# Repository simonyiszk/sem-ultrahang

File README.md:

# Ultrahangos hangszóró

## Célkitűzés 
A projekt során egy ultrahangos irányított hangszórót tervezünk és valósítunk meg először analóg, majd digitális elektronikai alkatrészek felhasználásával.
Az elkészült hangszórót standolásokon bemutatható kísérleti eszköznek szánjuk, az öncélú szórakozáson kívül (zenehallgatás) akusztikával kapcsolatos fizikai kísérletek szemléltetésére, mint például:
- hanghullámok terjedésének és tulajdonságainak vizsgálata
- ultrahangos lebegtetés

## Analóg verzió
A rendszer blokkvázlata az alábbi ábrán látható:

A jelforrást egyelőre nem specifikáltuk.
Az analóg verzióban PWM modulátort és a hozzá tartozó oszcillátort műveleti erősítőkkel valósítjuk meg.
Kapcsolóüzemű végerősítőfokozat gyanánt H-hidat, a prototípusban TC4427 típusú gate-meghajtó IC-t használunk. Hangszóróként az internetről rendelt 40 kHz rezonanciafrekvenciájú ultrahangos adó szolgál.

### Mérföldkövek

- [ ] **PWM modulátor műveleti erősítővel**
  - [X] Integrátor építése és mérése
  - [X] Hiszterézises komparátor építése és mérése
  - [X] Komplett prototípus megépítése breadboard-on
  - [ ] **Dokumentálás**
  - [ ] **Áramkörtervezés**
- [X] Jelforrás specifikációja
  - [X] Szükséges terveznivalók
- [X] Végfok
  - [X] H-híd tervezése (szükséges egyáltalán?)
- [ ] Hangszórómátrix
- [ ] Rendszerintegráció
  - [ ] NYÁK tervezés
  - [ ] Gyártás
  - [ ] Beültetés

### Side quest-ek
- [X] **Ultrahangos lebegtető**
  - [X] TC4427 tesztje
  - [X] **Oszcillátor aszimmetrikus táplálásának megoldása**
  - [X] **Hullámhossz meghatározása a pozicionáláshoz**
  - [X] Önjáró prototípus megépítése (amihez csak táp kell, és működik)
- [ ] Tápegység tervezése
  - TBD

## Digitális verzió
(Még nem tartunk itt... egyébként a [2025-ös tanfolyampanelt](https://github.com/simonyiszk/sem-armpanel-2025) szeretnénk hozzá használni.)

## Dokumentáció
A hierarchikus schematic dokumentációja [itt](./docs/hierarchia.md) érhető el.

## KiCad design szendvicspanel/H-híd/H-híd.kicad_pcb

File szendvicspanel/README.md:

# Szendvicspanel

## Megtervezendő:
 - [ ] board mérete
 - [ ] lábak száma, lábkiosztás az összes modult figyelembe véve (ld: [rendszerterv](../rendszerterv.txt))
 - [ ] legyenek-e átkonfigurálhatók a lábak (pl. jumperekkel)
 - [ ] analóg modul a jelgenerátorra
   - [ ] schematic
   - [ ] PCB
 - [ ] BOOST-konverteres tápegység
   - [ ] schematic
   - [ ] PCB
 - [ ] jelgenerátor PCB
 - [ ] H-híd + driver PCB
 - [ ] mikrokontroller PCB

## Mikrokontroller pinout

 - **a kép vízszintesen tükrözve van**
 - socketek kellenek neki
 - lehet-e neki tápot adni?

## WIP:
jelgenerátor modul PCB (ld: `jelgen.kicad_pro`)
 - opamp a REF feszültségen
 - PWM generátor
 - az analóg input jelenleg hanging:(
 - 10x10 cm, pazarló a hellyel
 - 2x10 pin, csak 4-et használ
 - egyoldalú, THT
 - teszt pontok még kellenek rá
 - még van mit pofozni rajta

H-híd + driver PCB (ld: `hbridge.kicad_pro`)
 - P-csatornás FET-ek a híd felére, vezérlőjelek átkötve
 - PCB még nincs

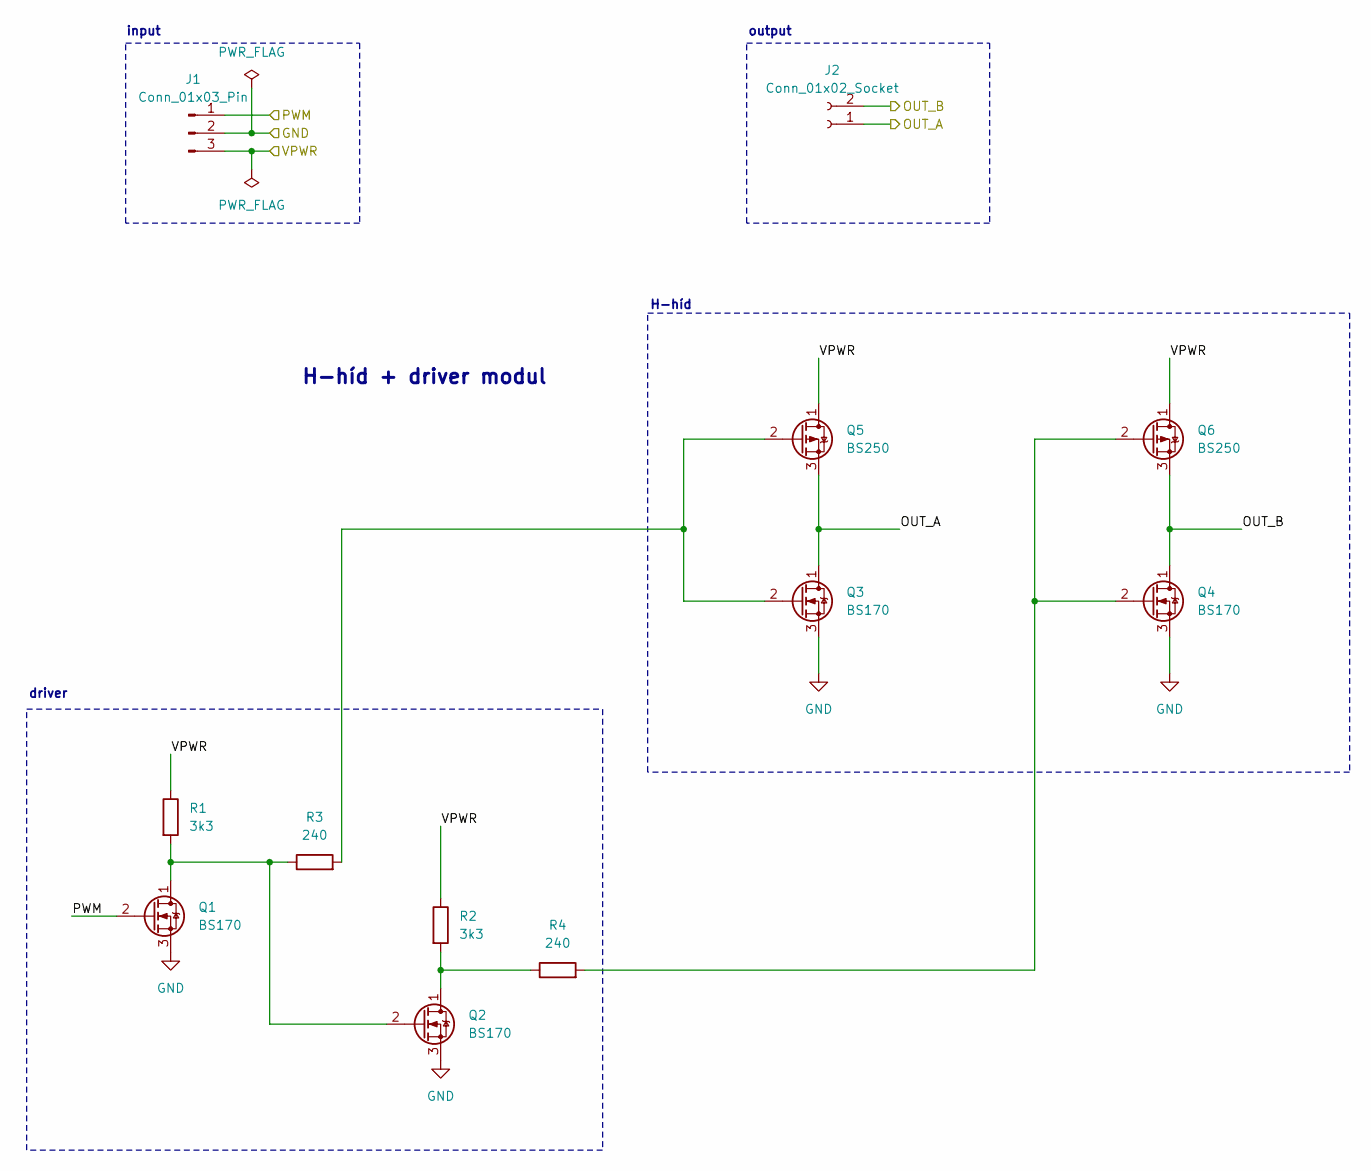
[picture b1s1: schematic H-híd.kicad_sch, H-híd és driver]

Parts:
J1: Conn_01x03_Pin; PinHeader_1x03_P2.54mm_Horizontal
J2: Conn_01x02_Socket; PinSocket_1x02_P2.54mm_Horizontal
Q1, Q2, Q3, Q4: BS170; TO-92_Inline
Q5, Q6: BS250; TO-92_Inline
R1, R2: 3k3; R_1210_3225Metric_Pad1.30x2.65mm_HandSolder
R3, R4: 240; R_1210_3225Metric_Pad1.30x2.65mm_HandSolder

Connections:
/OUT_A: J2.1, Q3.1 (D), Q5.3 (S)
/OUT_B: J2.2, Q4.1 (D), Q6.3 (S)
/PWM: J1.1, Q1.2 (G)
/VPWR: J1.3, Q5.1 (D), Q6.1 (D), R1.1, R2.1
GND: J1.2, Q1.3 (S), Q2.3 (S), Q3.3 (S), Q4.3 (S)
unnamed: Q1.1 (D), Q2.2 (G), R1.2, R3.1
unnamed: Q2.1 (D), R2.2, R4.1
unnamed: Q3.2 (G), Q5.2 (G), R3.2
unnamed: Q4.2 (G), Q6.2 (G), R4.2

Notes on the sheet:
H-híd + driver modul
output
H-híd
driver
input

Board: 2 copper layers, 12 parts (4 on the bottom side), 9 nets, no tracks yet.

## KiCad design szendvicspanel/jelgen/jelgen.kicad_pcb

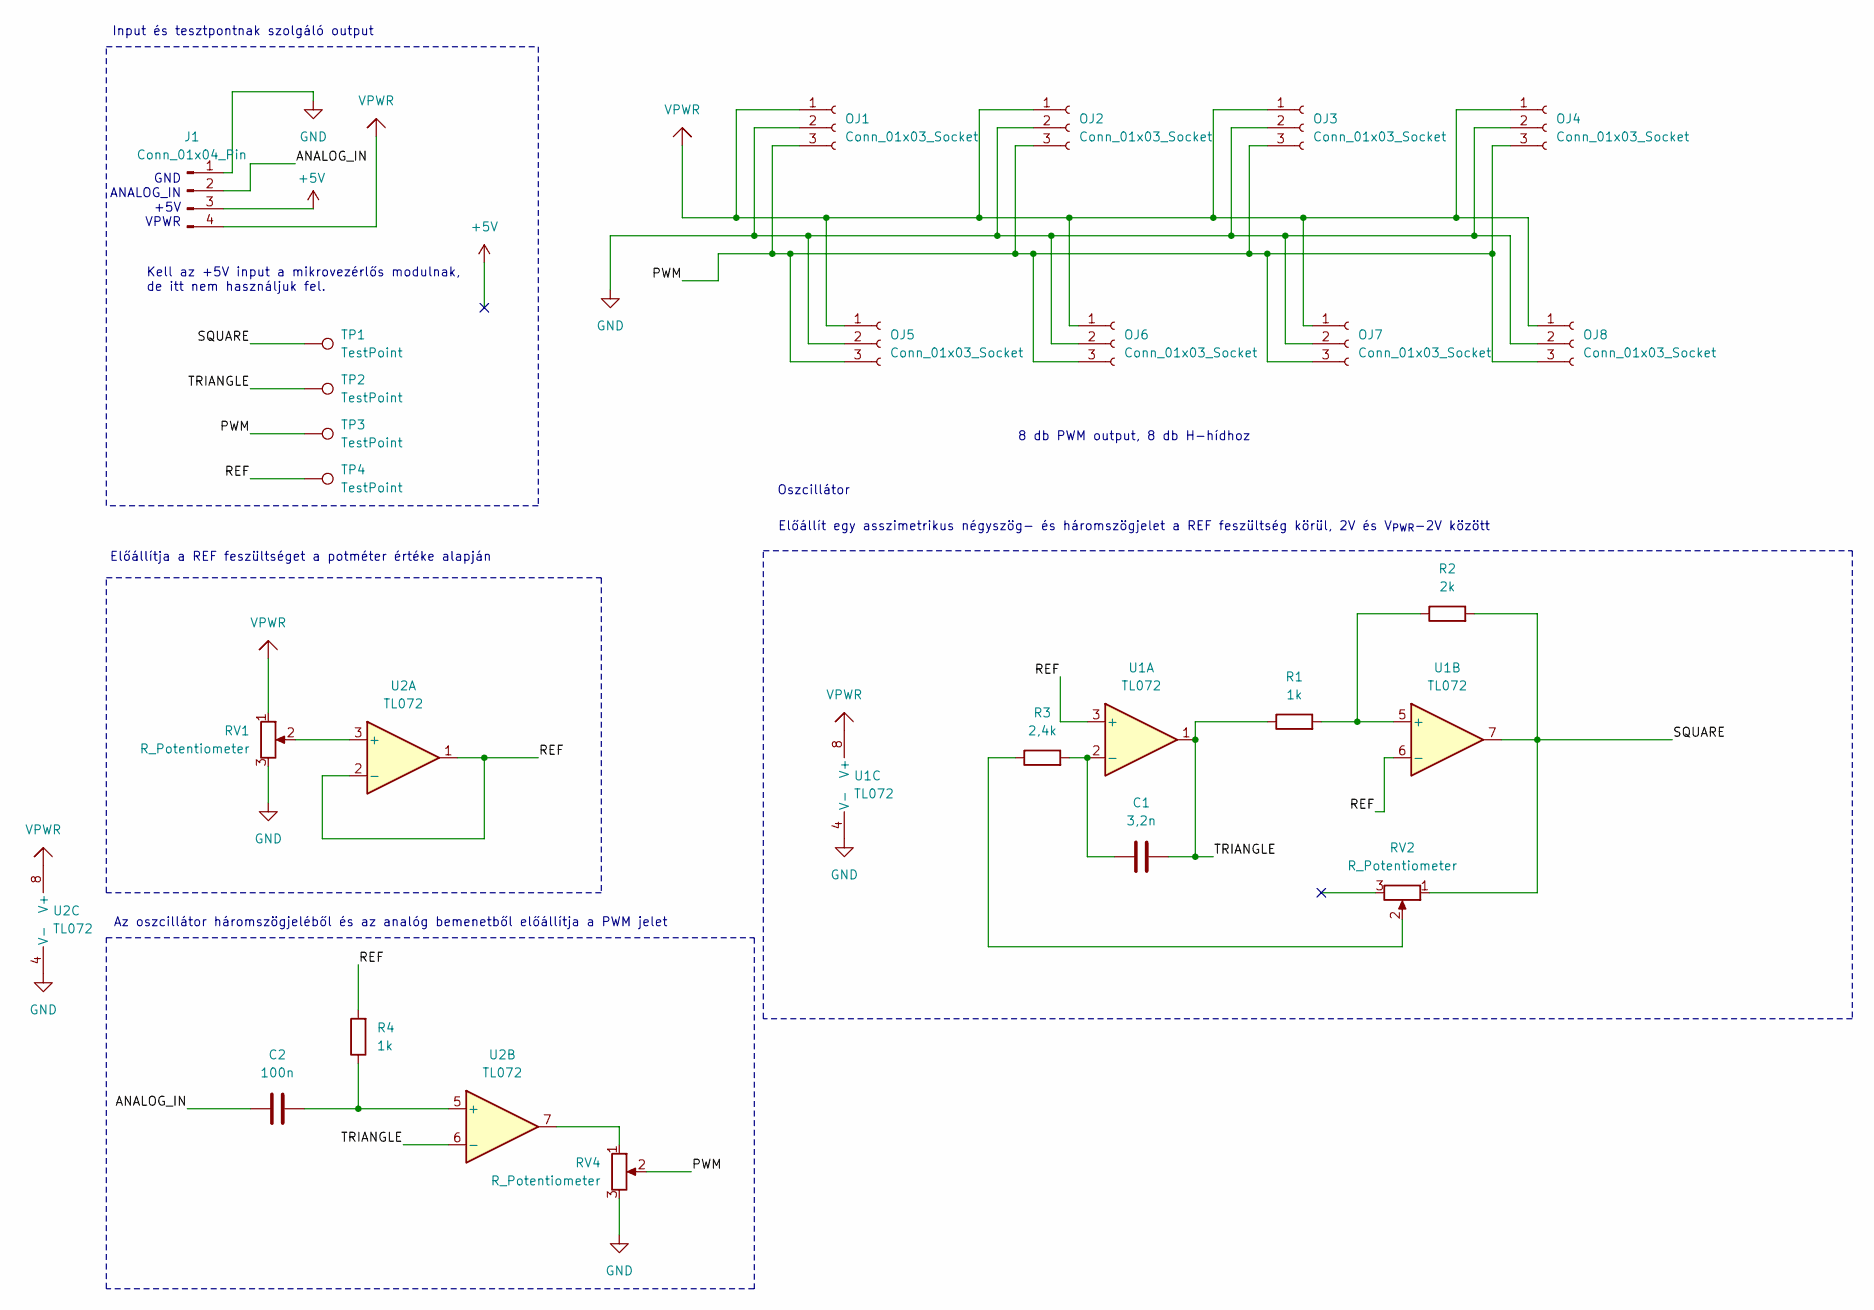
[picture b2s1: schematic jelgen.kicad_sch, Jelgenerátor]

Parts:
C1: 3,2n; C_Axial_L5.1mm_D3.1mm_P7.50mm_Horizontal
C2: 100n; C_Axial_L5.1mm_D3.1mm_P7.50mm_Horizontal
J1: Conn_01x04_Pin; PinHeader_1x04_P2.54mm_Horizontal
OJ1, OJ2, OJ3, OJ4, OJ5, OJ6, OJ7, OJ8: Conn_01x03_Socket; sajat_pin3
R1, R4: 1k; R_Axial_DIN0204_L3.6mm_D1.6mm_P5.08mm_Horizontal
R2: 2k; R_Axial_DIN0204_L3.6mm_D1.6mm_P5.08mm_Horizontal
R3: 2,4k; R_Axial_DIN0204_L3.6mm_D1.6mm_P5.08mm_Horizontal
RV1, RV2, RV4: R_Potentiometer; Potentiometer_Bourns_3266Y_Vertical
TP1, TP2, TP3, TP4: TestPoint; PinHeader_1x01_P2.54mm_Vertical
U1, U2: TL072; DIP-8_W7.62mm_LongPads

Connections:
+5V: J1.3
/ANALOG_IN: C2.1, J1.2
/PWM: OJ1.3, OJ2.3, OJ3.3, OJ4.3, OJ5.3, OJ6.3, OJ7.3, OJ8.3, RV4.2, TP3.1 (1_1)
/REF: R4.2, TP4.1 (1_1), U1.3 (+), U1.6 (-), U2.1, U2.2 (-)
/SQUARE: R2.2, RV2.1, TP1.1 (1_1), U1.7
/TRIANGLE: C1.2, R1.1, TP2.1 (1_1), U1.1, U2.6 (-)
GND: J1.1, OJ1.2, OJ2.2, OJ3.2, OJ4.2, OJ5.2, OJ6.2, OJ7.2, OJ8.2, RV1.3, RV4.3, U1.4 (V-), U2.4 (V-)
unnamed: R3.1, RV2.2
unnamed: RV4.1, U2.7
unnamed: C1.1, R3.2, U1.2 (-)
unnamed: R1.2, R2.1, U1.5 (+)
unnamed: RV1.2, U2.3 (+)
unnamed: C2.2, R4.1, U2.5 (+)
VPWR: J1.4, OJ1.1, OJ2.1, OJ3.1, OJ4.1, OJ5.1, OJ6.1, OJ7.1, OJ8.1, RV1.1, U1.8 (V+), U2.8 (V+)

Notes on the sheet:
Input és tesztpontnak szolgáló output
GND ANALOG_IN +5V VPWR
Az oszcillátor háromszögjeléből és az analóg bemenetből előállítja a PWM jelet
Előállít egy asszimetrikus négyszög- és háromszögjelet a REF feszültség körül, 2V és V_{PWR}-2V között
Előállítja a REF feszültséget a potméter értéke alapján
Kell az +5V input a mikrovezérlős modulnak, de itt nem használjuk fel.
8 db PWM output, 8 db H-hídhoz
Oszcillátor

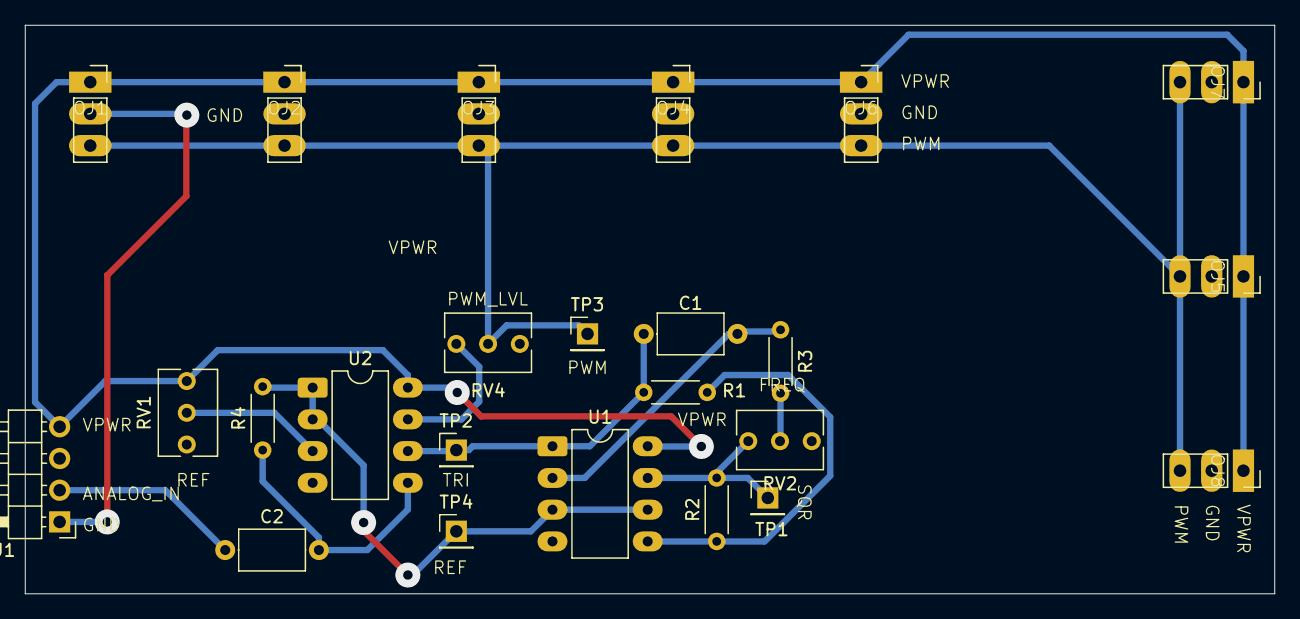
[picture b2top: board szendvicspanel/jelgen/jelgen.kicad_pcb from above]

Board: 2 copper layers, 100.0 x 45.5 mm, 24 parts (0 on the bottom side), 13 nets.

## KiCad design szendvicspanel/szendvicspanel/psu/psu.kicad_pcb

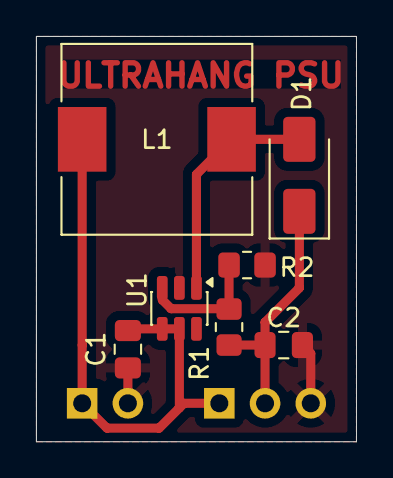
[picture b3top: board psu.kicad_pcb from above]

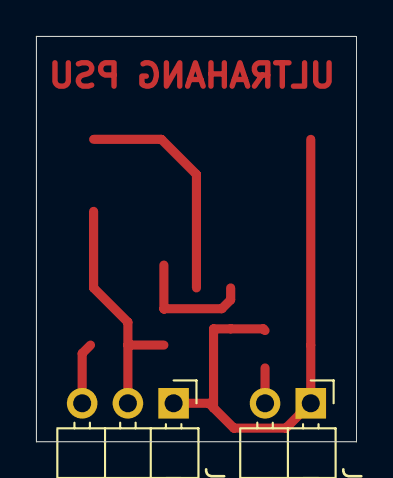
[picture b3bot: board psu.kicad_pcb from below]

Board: 2 copper layers, 17.8 x 22.5 mm, 9 parts (2 on the bottom side), 5 nets.

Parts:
C1, C2: 22u; C_0805_2012Metric_Pad1.18x1.45mm_HandSolder
D1: SS24; D_SMA
J1: Conn_01x02; PinHeader_1x02_P2.54mm_Horizontal
J2: Conn_01x03; PinHeader_1x03_P2.54mm_Horizontal
L1: 4u7; L_10.4x10.4_H4.8
R1: 100k; R_0805_2012Metric_Pad1.20x1.40mm_HandSolder
R2: 3k9; R_0805_2012Metric_Pad1.20x1.40mm_HandSolder
U1: MT3608; SOT-23-6

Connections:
+5V: C1.1, J1.1, J2.1, L1.1, U1.4 (EN), U1.5 (IN)
/VPWR: C2.1, D1.1 (K), J2.2, R1.1
GND: C1.2, C2.2, J1.2, J2.3, R2.2, U1.2 (GND)
unnamed: D1.2 (A), L1.2, U1.1 (SW)
unnamed: R1.2, R2.1, U1.3 (FB)

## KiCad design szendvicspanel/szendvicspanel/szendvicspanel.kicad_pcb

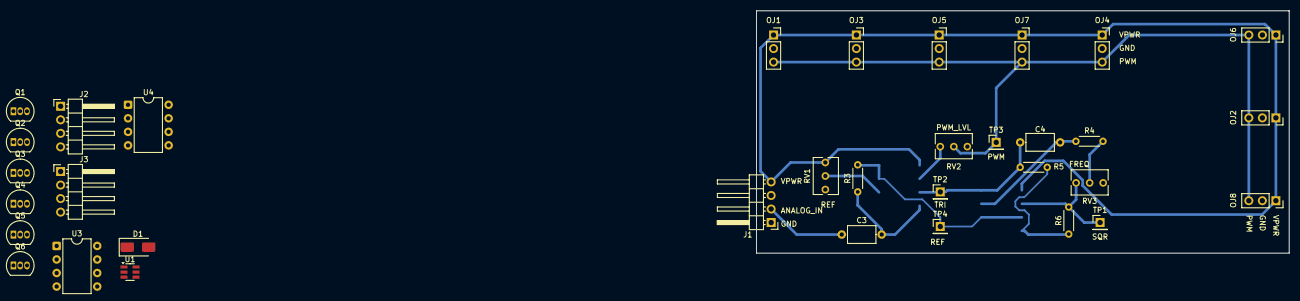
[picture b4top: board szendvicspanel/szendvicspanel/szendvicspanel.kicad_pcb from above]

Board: 2 copper layers, 100.0 x 45.5 mm, 34 parts (0 on the bottom side), 20 nets.

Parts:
C3: 100n; C_Axial_L5.1mm_D3.1mm_P7.50mm_Horizontal
C4: 3,2n; C_Axial_L5.1mm_D3.1mm_P7.50mm_Horizontal
D1: SS24; D_SMA
J1, J2, J3: Conn_01x04_Pin; PinHeader_1x04_P2.54mm_Horizontal
OJ1, OJ2, OJ3, OJ4, OJ5, OJ6, OJ7, OJ8: Conn_01x03_Socket; PinSocket_1x03_P2.54mm_Vertical
Q1, Q2, Q4, Q6: BS170; TO-92_Inline
Q3, Q5: BS250; TO-92_Inline
R3, R5: 1k; R_Axial_DIN0204_L3.6mm_D1.6mm_P5.08mm_Horizontal
R4: 2,4k; R_Axial_DIN0204_L3.6mm_D1.6mm_P5.08mm_Horizontal
R6: 2k; R_Axial_DIN0204_L3.6mm_D1.6mm_P5.08mm_Horizontal
RV1, RV2, RV3: R_Potentiometer; Potentiometer_Bourns_3266Y_Vertical
TP1, TP2, TP3, TP4: TestPoint; PinHeader_1x01_P2.54mm_Vertical
U1: MT3608; SOT-23-6
U3, U4: TL072; DIP-8_W7.62mm

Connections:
+5V: U1.4 (EN), U1.5 (IN)
/Analóg interfész/+5V_IN: J1.3, J2.3, J3.3
/Analóg interfész/ANALOG_OUT: C3.1, J1.2, J3.2, U4.1
/H-híd + driver/OUT_A: Q3.3 (S), Q4.1 (D)
/H-híd + driver/OUT_B: Q5.3 (S), Q6.1 (D)
/H-híd + driver/VPWR: Q3.1 (D), Q5.1 (D)
/analóg jelgen + PWM/OUT.PWM1: OJ1.3, OJ2.3, OJ3.3, OJ4.3, OJ5.3, OJ6.3, OJ7.3, OJ8.3, RV2.2, TP3.1
/analóg jelgen + PWM/REF: R3.2, TP4.1, U3.3 (+), U3.6 (-)
/analóg jelgen + PWM/SQUARE: R6.2, RV3.1, TP1.1, U3.7
/analóg jelgen + PWM/TRIANGLE: C4.2, R5.1, TP2.1, U3.1
GND: J1.1, J2.1, J3.1, OJ1.2, OJ2.2, OJ3.2, OJ4.2, OJ5.2, OJ6.2, OJ7.2, OJ8.2, Q1.3 (S), Q2.3 (S), Q4.3 (S), Q6.3 (S), RV1.3, RV2.3, U1.2 (GND), U3.4 (V-), U4.4 (V-)
unnamed: D1.2 (A), U1.1 (SW)
unnamed: Q1.1 (D), Q2.2 (G)
unnamed: Q3.2 (G), Q4.2 (G)
unnamed: Q5.2 (G), Q6.2 (G)
unnamed: R4.1, RV3.2
unnamed: C3.2, R3.1
unnamed: C4.1, R4.2, U3.2 (-)
unnamed: R5.2, R6.1, U3.5 (+)
VPWR: D1.1 (K), J1.4, J2.4, J3.4, OJ1.1, OJ2.1, OJ3.1, OJ4.1, OJ5.1, OJ6.1, OJ7.1, OJ8.1, RV1.1, U3.8 (V+), U4.8 (V+)

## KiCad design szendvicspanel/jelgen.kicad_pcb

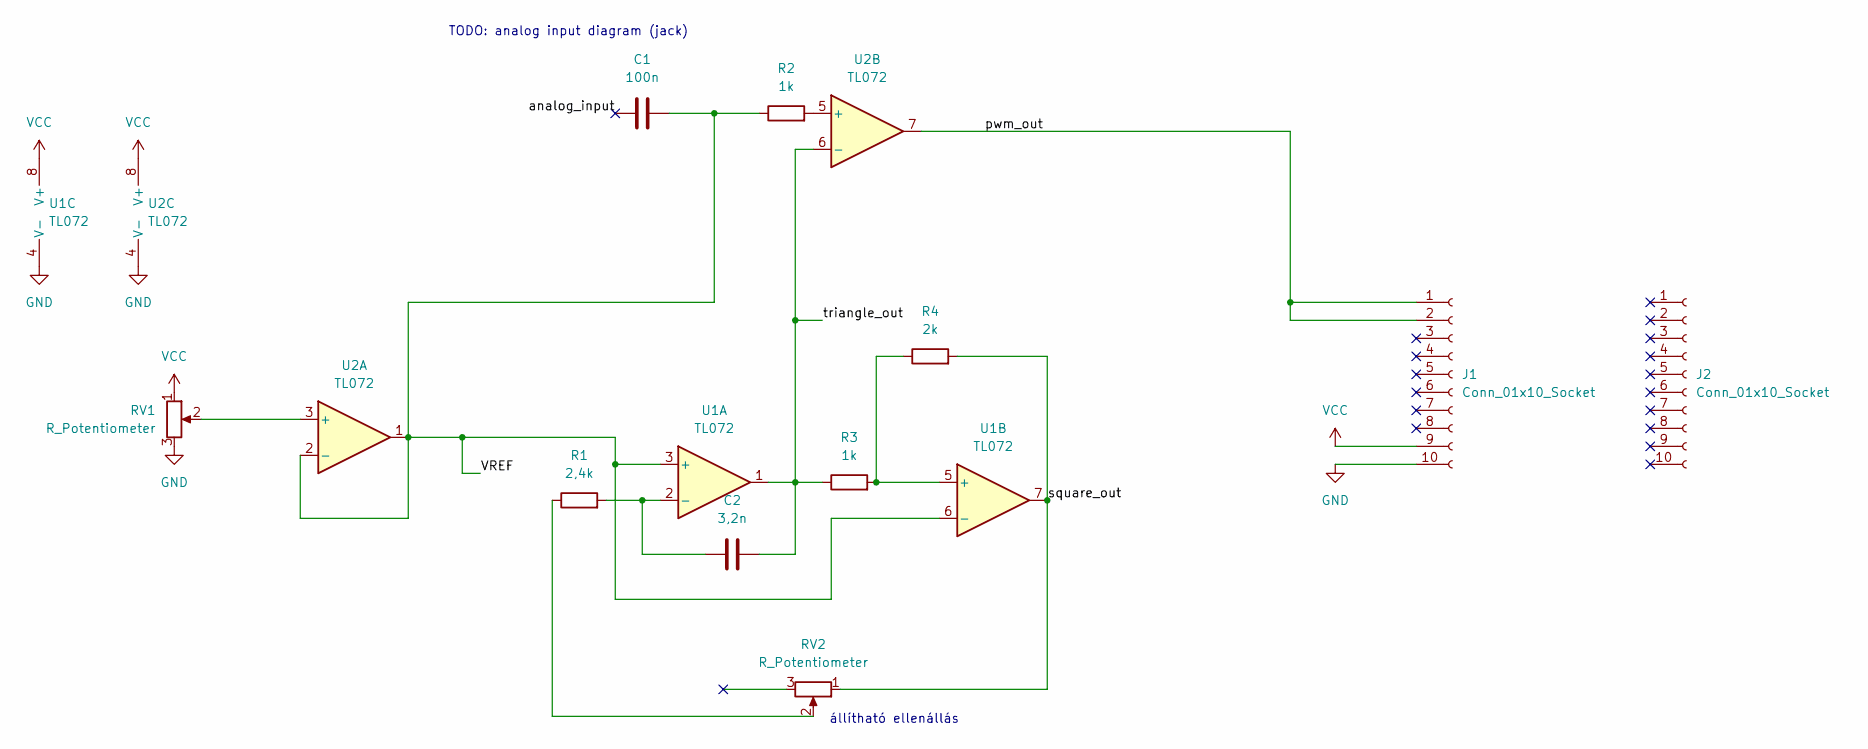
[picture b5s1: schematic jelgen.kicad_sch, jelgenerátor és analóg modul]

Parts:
C1: 100n; C_Axial_L3.8mm_D2.6mm_P7.50mm_Horizontal
C2: 3,2n; C_Axial_L3.8mm_D2.6mm_P7.50mm_Horizontal
J1, J2: Conn_01x10_Socket; PinHeader_1x10_P2.54mm_Vertical
R1: 2,4k; R_Axial_DIN0204_L3.6mm_D1.6mm_P5.08mm_Horizontal
R2, R3: 1k; R_Axial_DIN0204_L3.6mm_D1.6mm_P5.08mm_Horizontal
R4: 2k; R_Axial_DIN0204_L3.6mm_D1.6mm_P5.08mm_Horizontal
RV1, RV2: R_Potentiometer; Potentiometer_Vishay_T93YA_Vertical
U1, U2: TL072; DIP-8_W7.62mm_Socket

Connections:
/VREF: C1.2, R2.1, U1.3 (+), U1.6 (-), U2.1, U2.2 (-)
/analog_input: C1.1
/pwm_out: J1.1, J1.2, U2.7
/square_out: R4.2, RV2.1, U1.7
/triangle_out: C2.2, R3.1, U1.1, U2.6 (-)
GND: J1.10, RV1.3, U1.4 (V-), U2.4 (V-)
unnamed: R1.1, RV2.2
unnamed: C2.1, R1.2, U1.2 (-)
unnamed: R3.2, R4.1, U1.5 (+)
unnamed: RV1.2, U2.3 (+)
unnamed: R2.2, U2.5 (+)
VCC: J1.9, RV1.1, U1.8 (V+), U2.8 (V+)

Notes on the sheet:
állítható ellenállás
TODO: analog input diagram (jack)

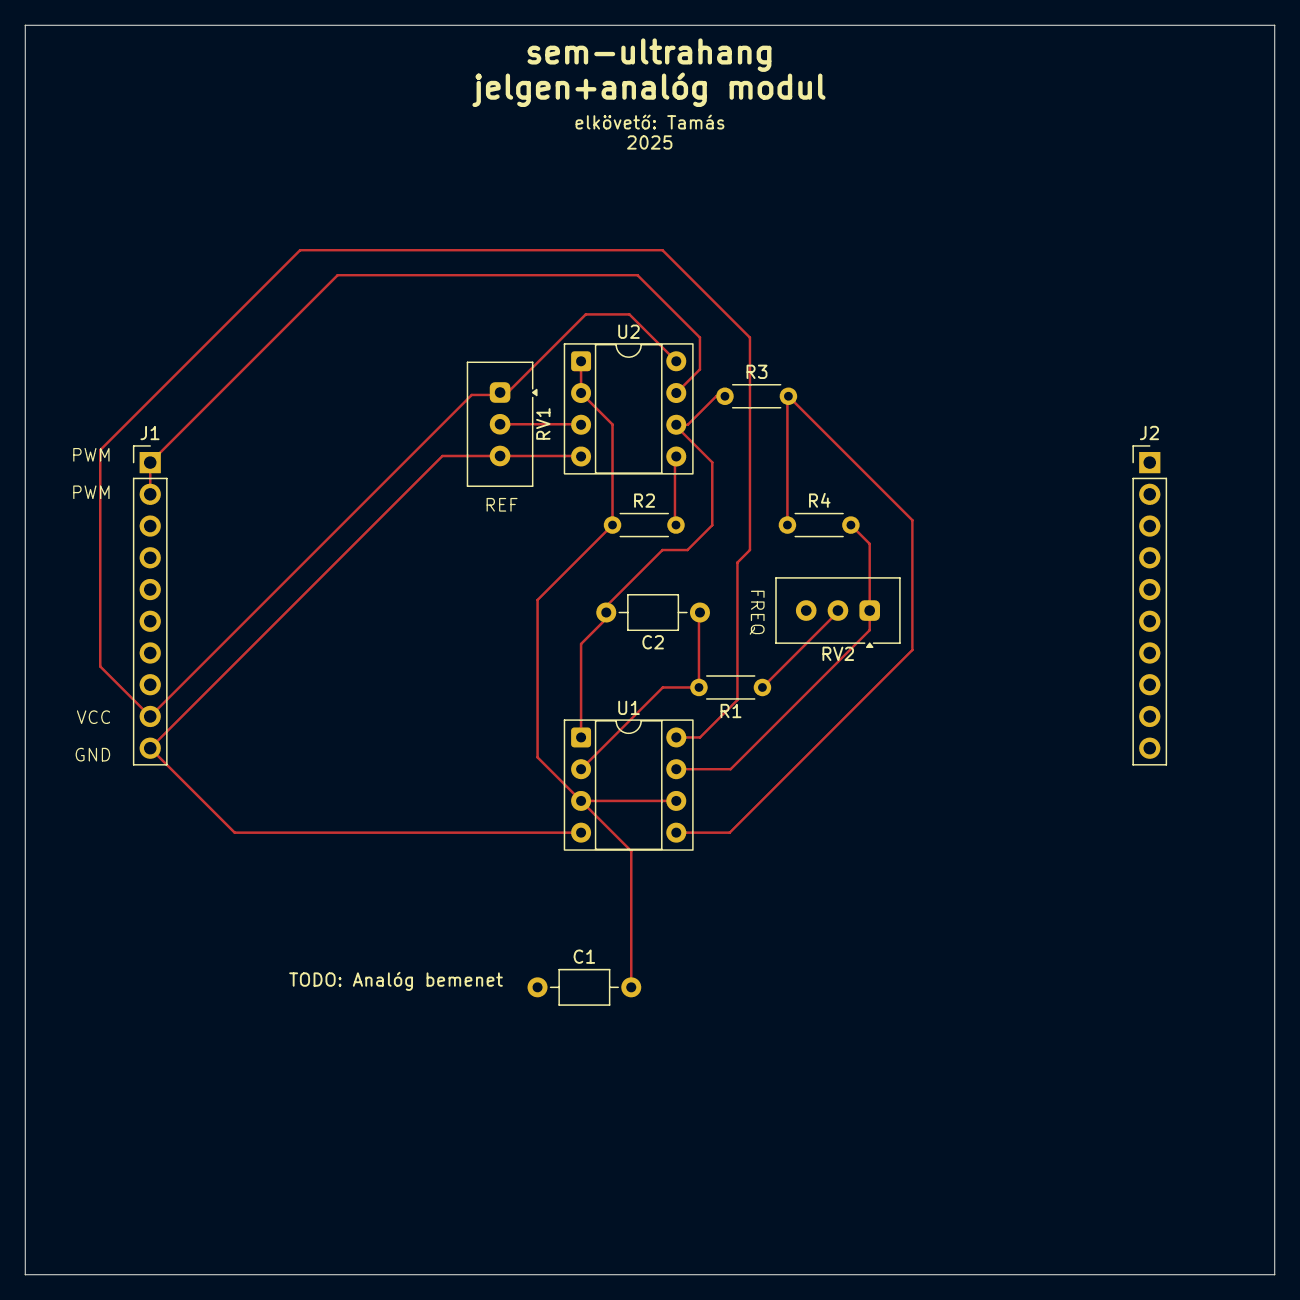
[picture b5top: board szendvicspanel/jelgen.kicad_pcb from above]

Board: 2 copper layers, 100.0 x 100.0 mm, 12 parts (0 on the bottom side), 11 nets.

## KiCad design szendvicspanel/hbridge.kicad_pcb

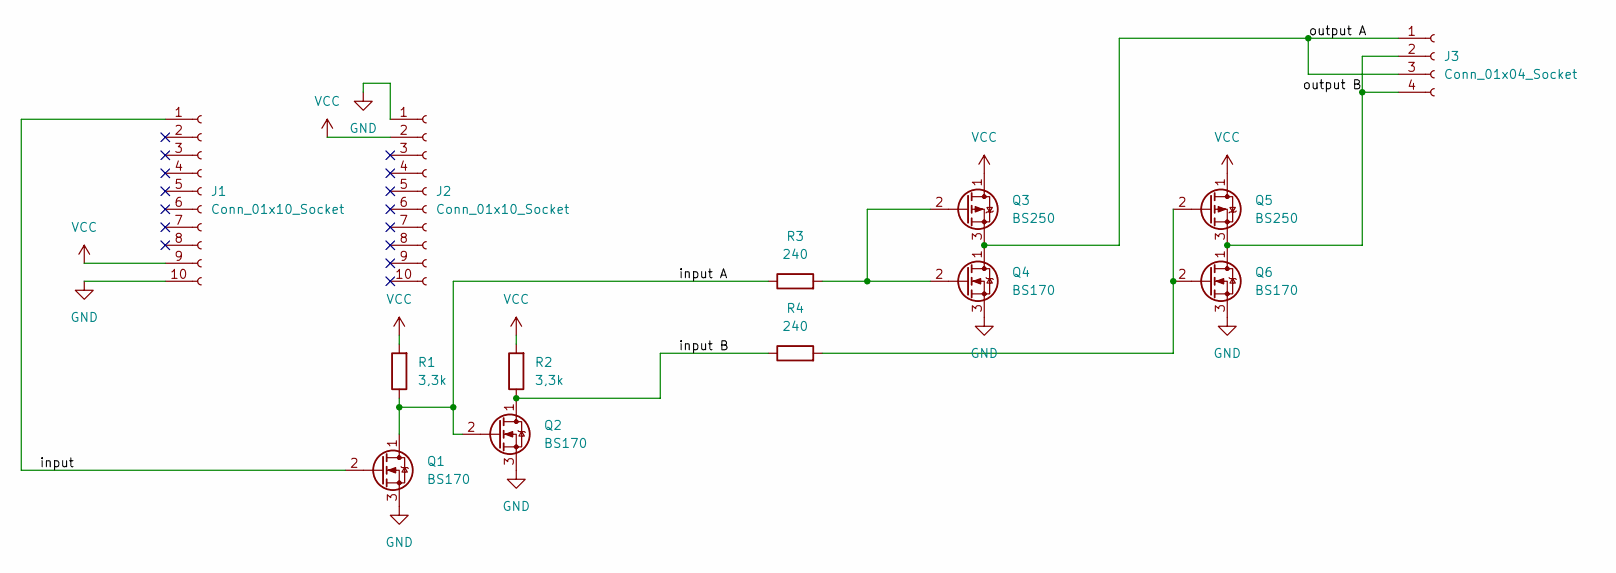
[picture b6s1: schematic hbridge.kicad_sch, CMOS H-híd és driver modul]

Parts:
J1, J2: Conn_01x10_Socket; PinHeader_1x10_P2.54mm_Vertical
J3: Conn_01x04_Socket; PinHeader_1x04_P2.54mm_Horizontal
Q1, Q2, Q4, Q6: BS170; TO-92_Inline
Q3, Q5: BS250; TO-92_Inline
R1, R2: 3,3k; R_Axial_DIN0204_L3.6mm_D1.6mm_P5.08mm_Horizontal
R3, R4: 240; R_Axial_DIN0204_L3.6mm_D1.6mm_P5.08mm_Horizontal

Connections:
/input: J1.1, Q1.2 (G)
/input A: Q1.1 (D), Q2.2 (G), R1.1, R3.1
/input B: Q2.1 (D), R2.1, R4.1
/output A: J3.1, J3.3, Q3.3 (S), Q4.1 (D)
/output B: J3.2, J3.4, Q5.3 (S), Q6.1 (D)
GND: J1.10, J2.1, Q1.3 (S), Q2.3 (S), Q4.3 (S), Q6.3 (S)
unnamed: Q3.2 (G), Q4.2 (G), R3.2
unnamed: Q5.2 (G), Q6.2 (G), R4.2
VCC: J1.9, J2.2, Q3.1 (D), Q5.1 (D), R1.2, R2.2

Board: 2 copper layers, 13 parts (0 on the bottom side), 9 nets, no tracks yet.

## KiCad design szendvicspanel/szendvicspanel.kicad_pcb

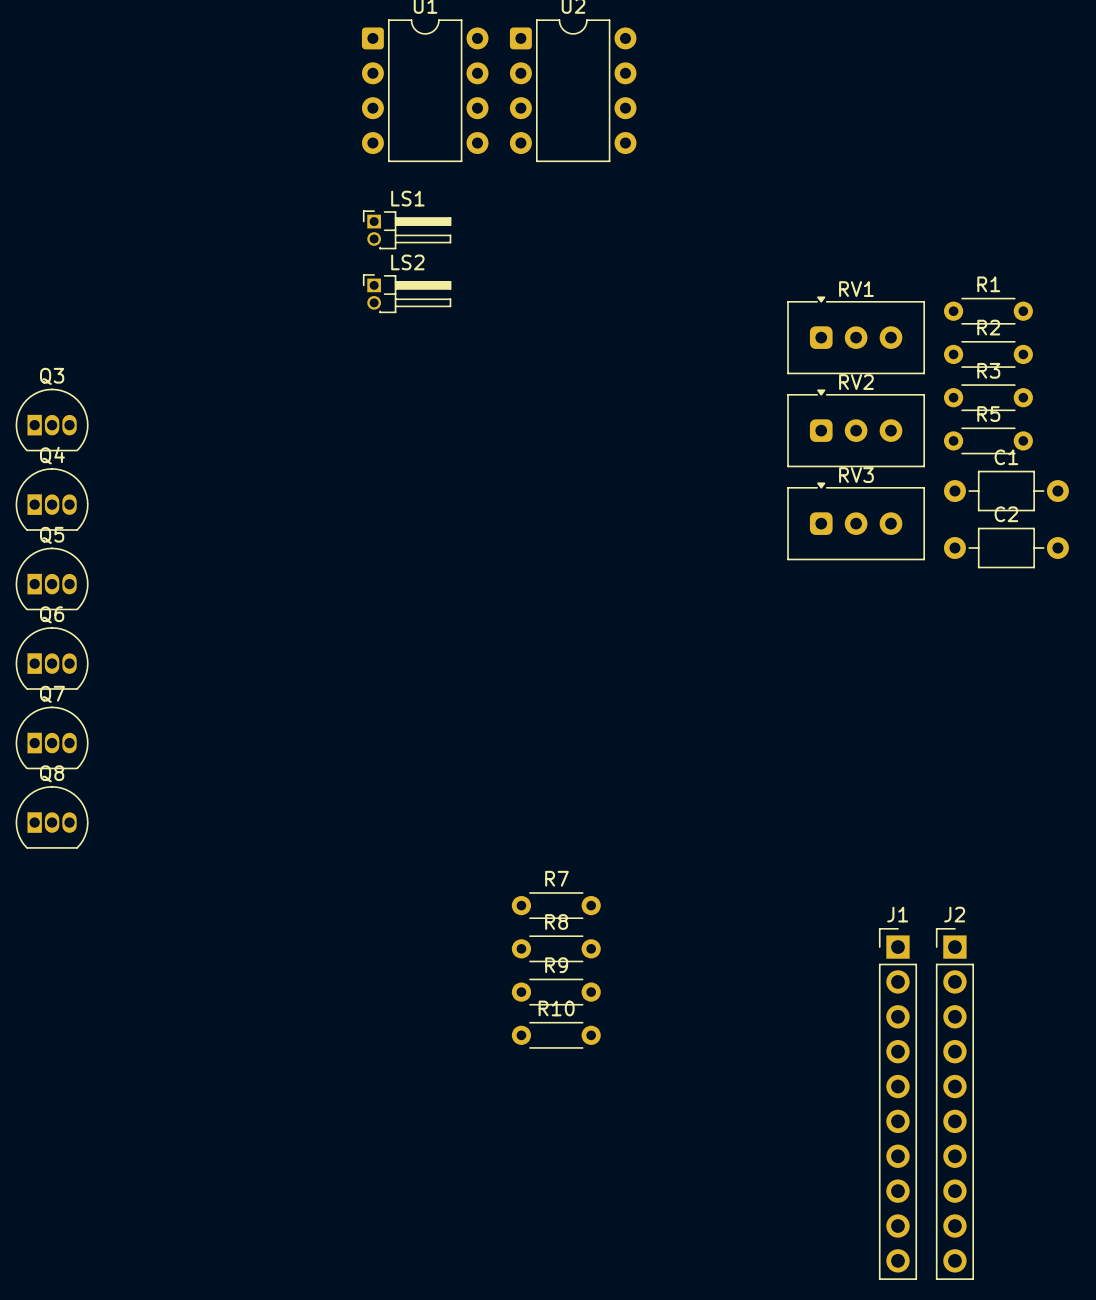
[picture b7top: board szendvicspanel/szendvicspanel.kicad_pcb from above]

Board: 2 copper layers, 25 parts (0 on the bottom side), 20 nets, no tracks yet.

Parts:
C1: 3,2n; C_Axial_L3.8mm_D2.6mm_P7.50mm_Horizontal
C2: 100n; C_Axial_L3.8mm_D2.6mm_P7.50mm_Horizontal
J1, J2: Conn_01x10_Socket; PinHeader_1x10_P2.54mm_Vertical
LS1, LS2: Speaker_Ultrasound; PinHeader_1x02_P1.27mm_Horizontal
Q3, Q4, Q7, Q8: BS170; TO-92_Inline
Q5, Q6: BS250; TO-92_Inline
R1: 2,4k; R_Axial_DIN0204_L3.6mm_D1.6mm_P5.08mm_Horizontal
R2, R5: 1k; R_Axial_DIN0204_L3.6mm_D1.6mm_P5.08mm_Horizontal
R3: 2k; R_Axial_DIN0204_L3.6mm_D1.6mm_P5.08mm_Horizontal
R7, R8: 240; R_Axial_DIN0204_L3.6mm_D1.6mm_P5.08mm_Horizontal
R9, R10: 3,3k; R_Axial_DIN0204_L3.6mm_D1.6mm_P5.08mm_Horizontal
RV1, RV2, RV3: R_Potentiometer; Potentiometer_Vishay_T93YA_Vertical
U1, U2: TL072; DIP-8_W7.62mm

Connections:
+12V: Q5.1 (D), Q6.1 (D), R9.2, R10.2
/CMOS H-híd és driver modul/input A: Q7.1 (D), Q8.2 (G), R7.1, R9.1
/CMOS H-híd és driver modul/input B: Q8.1 (D), R8.1, R10.1
/CMOS H-híd és driver modul/output A: LS1.1, LS2.1, Q3.1 (D), Q5.3 (S)
/CMOS H-híd és driver modul/output B: LS1.2, LS2.2, Q4.1 (D), Q6.3 (S)
/Jelgenerátor és analóg modul/GND: J1.10, RV1.1, RV2.3, U1.4 (V-), U2.4 (V-)
/Jelgenerátor és analóg modul/VIN: J1.9, RV2.1, U1.8 (V+), U2.8 (V+)
/Jelgenerátor és analóg modul/VREF: C2.2, R5.1, U1.3 (+), U1.6 (-), U2.1, U2.2 (-)
/Jelgenerátor és analóg modul/pwm_out: J1.1, U2.7
/Jelgenerátor és analóg modul/square_out: J1.2, RV1.2
/Jelgenerátor és analóg modul/triangle: C1.2, R2.1, U1.1, U2.6 (-)
GND: Q3.3 (S), Q4.3 (S), Q7.3 (S), Q8.3 (S)
unnamed: Q3.2 (G), Q5.2 (G), R7.2
unnamed: Q4.2 (G), Q6.2 (G), R8.2
unnamed: R1.1, RV3.2
unnamed: R3.2, RV1.3, RV3.1, U1.7
unnamed: C1.1, R1.2, U1.2 (-)
unnamed: R2.2, R3.1, U1.5 (+)
unnamed: RV2.2, U2.3 (+)
unnamed: R5.2, U2.5 (+)

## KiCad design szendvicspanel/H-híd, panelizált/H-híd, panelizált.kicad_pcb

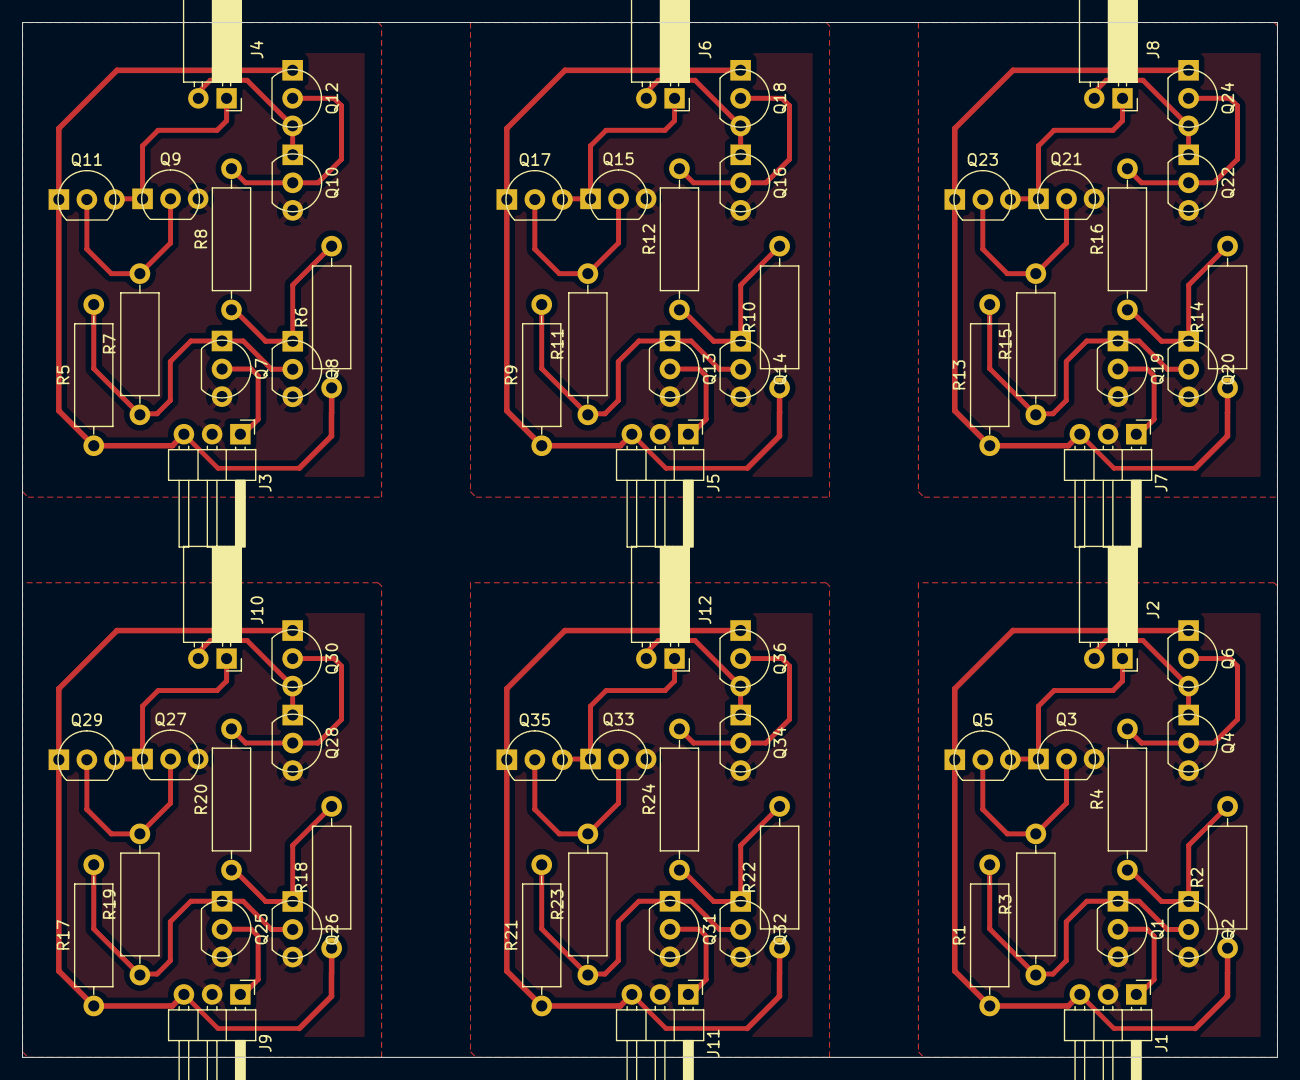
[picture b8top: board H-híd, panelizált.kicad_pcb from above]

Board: 2 copper layers, 112.9 x 93.1 mm, 72 parts (0 on the bottom side), 9 nets.

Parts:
J1, J3, J5, J7, J9, J11: Conn_01x03_Pin; PinHeader_1x03_P2.54mm_Horizontal
J2, J4, J6, J8, J10, J12: Conn_01x02_Socket; PinSocket_1x02_P2.54mm_Horizontal
Q1, Q2, Q3, Q4, Q7, Q8, Q9, Q10, Q13, Q14, Q15, Q16, Q19, Q20, Q21, Q22, Q25, Q26, Q27, Q28, Q31, Q32, Q33, Q34: BS170; TO-92_Inline
Q5, Q6, Q11, Q12, Q17, Q18, Q23, Q24, Q29, Q30, Q35, Q36: BS250; TO-92_Inline
R1, R2, R5, R6, R9, R10, R13, R14, R17, R18, R21, R22: 3k3; R_Axial_DIN0309_L9.0mm_D3.2mm_P12.70mm_Horizontal
R3, R4, R7, R8, R11, R12, R15, R16, R19, R20, R23, R24: 240; R_Axial_DIN0309_L9.0mm_D3.2mm_P12.70mm_Horizontal

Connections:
/OUT_A: J2.1, J4.1, J6.1, J8.1, J10.1, J12.1, Q3.1 (D), Q5.3 (S), Q9.1 (D), Q11.3 (S), Q15.1 (D), Q17.3 (S), Q21.1 (D), Q23.3 (S), Q27.1 (D), Q29.3 (S), Q33.1 (D), Q35.3 (S)
/OUT_B: J2.2, J4.2, J6.2, J8.2, J10.2, J12.2, Q4.1 (D), Q6.3 (S), Q10.1 (D), Q12.3 (S), Q16.1 (D), Q18.3 (S), Q22.1 (D), Q24.3 (S), Q28.1 (D), Q30.3 (S), Q34.1 (D), Q36.3 (S)
/PWM: J1.1, J3.1, J5.1, J7.1, J9.1, J11.1, Q1.2 (G), Q7.2 (G), Q13.2 (G), Q19.2 (G), Q25.2 (G), Q31.2 (G)
/VPWR: J1.3, J3.3, J5.3, J7.3, J9.3, J11.3, Q5.1 (D), Q6.1 (D), Q11.1 (D), Q12.1 (D), Q17.1 (D), Q18.1 (D), Q23.1 (D), Q24.1 (D), Q29.1 (D), Q30.1 (D), Q35.1 (D), Q36.1 (D), R1.1, R2.1, R5.1, R6.1, R9.1, R10.1, R13.1, R14.1, R17.1, R18.1, R21.1, R22.1
GND: J1.2, J3.2, J5.2, J7.2, J9.2, J11.2, Q1.3 (S), Q2.3 (S), Q3.3 (S), Q4.3 (S), Q7.3 (S), Q8.3 (S), Q9.3 (S), Q10.3 (S), Q13.3 (S), Q14.3 (S), Q15.3 (S), Q16.3 (S), Q19.3 (S), Q20.3 (S), Q21.3 (S), Q22.3 (S), Q25.3 (S), Q26.3 (S), Q27.3 (S), Q28.3 (S), Q31.3 (S), Q32.3 (S), Q33.3 (S), Q34.3 (S)
unnamed: Q1.1 (D), Q2.2 (G), Q7.1 (D), Q8.2 (G), Q13.1 (D), Q14.2 (G), Q19.1 (D), Q20.2 (G), Q25.1 (D), Q26.2 (G), Q31.1 (D), Q32.2 (G), R1.2, R3.1, R5.2, R7.1, R9.2, R11.1, R13.2, R15.1, R17.2, R19.1, R21.2, R23.1
unnamed: Q2.1 (D), Q8.1 (D), Q14.1 (D), Q20.1 (D), Q26.1 (D), Q32.1 (D), R2.2, R4.1, R6.2, R8.1, R10.2, R12.1, R14.2, R16.1, R18.2, R20.1, R22.2, R24.1
unnamed: Q3.2 (G), Q5.2 (G), Q9.2 (G), Q11.2 (G), Q15.2 (G), Q17.2 (G), Q21.2 (G), Q23.2 (G), Q27.2 (G), Q29.2 (G), Q33.2 (G), Q35.2 (G), R3.2, R7.2, R11.2, R15.2, R19.2, R23.2
unnamed: Q4.2 (G), Q6.2 (G), Q10.2 (G), Q12.2 (G), Q16.2 (G), Q18.2 (G), Q22.2 (G), Q24.2 (G), Q28.2 (G), Q30.2 (G), Q34.2 (G), Q36.2 (G), R4.2, R8.2, R12.2, R16.2, R20.2, R24.2

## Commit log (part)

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2025-04-18 Modulatortervrajz
2025-06-26 Lebegtető kapcsrajz
2025-06-26 Update README.md
    Update mérföldkövek
2025-08-18 Add simulation files
2025-08-22 H-híd és jelgenerátor frissítése
2025-08-22 Projekt átnevezése
2025-08-22 Footprintek
2025-08-22 Jelgenerátor layer schematic
2025-08-22 Nem használt H-bridge driver schematic törlése
2025-08-23 Jelgenerátor layer, README, .gitignore
2025-08-26 KiCAD Rendszerterv
2025-08-26 ANALOG_IN a mikrokontrolleres modulra is
2025-08-29 #5-ös issue, H-híd és driver modul
2025-08-30 Jelgenerátor terv
2025-09-01 PCB sketch 1
2025-09-01 PCB sketch 2
2025-09-04 Ground plane, output array áttervezés, input horizontal footprint
2025-09-04 Fölösleges fájlok szűrése .gitignore-al
2025-09-04 Jelgenerátor schematic szépítése
2025-09-05 H-híd schematic módosítás
2025-09-06 Create temp
2025-09-06 H-híd PCB
2025-09-08 Add PSU schematic
2025-09-09 KiCAD .gitignore
2025-09-09 Ignorált fájlok törlése a repoból
2025-09-09 Ignorált fájlok törlése a jelgen branchről
2025-09-09 VPWR szimbólum
2025-09-09 Jack és magas szintű terv
2025-09-11 takartás
2025-09-11 Modify component values
2025-09-16 Analóg interfész SPICE sketch
2025-09-16 SPICE .gitignore
2025-10-21 Analóg interfész a nagy spice szimulációba
2025-10-24 KiCAD analóg interfész
2025-10-30 Stereo -> mono WIP
2025-11-07 átláthatóbb kapcsrajz
2026-03-06 Add +5V output to psu.sch
2026-03-07 .log, .raw gitignore
2026-03-07 Átalakítás a H-híd panel szélességére, hanging +5V input pin
2026-03-07 [Kész] H-híd panel magasság, mérések, átrendezés
2026-03-07 Jelgenerátor dokumentáció
2026-03-07 Analóg jelgen schematic copy+paste, output busz, analóg interfész pinjeinek frissítése
2026-03-07 Hierarchika dokumentáció
2026-03-07 H-híd dokumentáció
2026-03-17 Dokumentáció, Bandpass WIP
2026-03-19 Analóg interfész dokumentáció
2026-03-19 Linkek
2026-03-19 Formázási hibák javítása a doksiban
2026-03-19 Átstrukturálás hierarchikus PCB-hez
2026-03-23 Add PSU PCB
2026-03-31 Analóg jelgen fix WIP
2026-03-31 Analóg jelgen fix
2026-03-31 Jelgen doksi frissítés
2026-03-31 Jelgen plot
2026-05-10 A H-hidat picit átdizájnoltam
2026-05-10 A panelizált H-hidakat létrehoztam
